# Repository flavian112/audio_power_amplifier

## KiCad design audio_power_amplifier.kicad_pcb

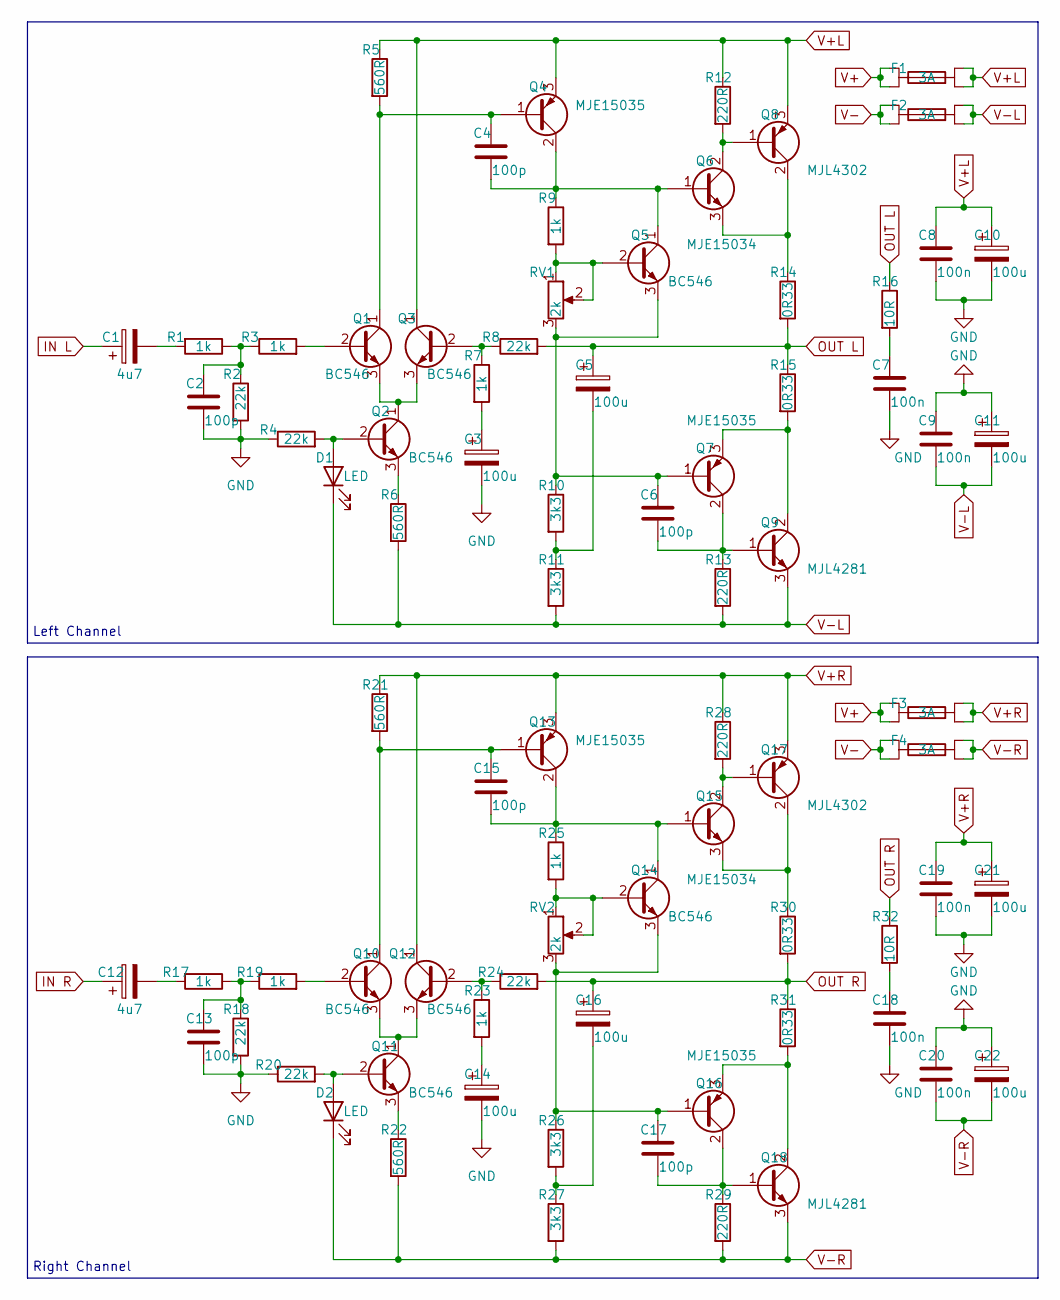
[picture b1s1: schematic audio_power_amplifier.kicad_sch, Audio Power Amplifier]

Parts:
C1, C12: 4u7; CP_Radial_D5.0mm_P2.00mm
C2, C4, C6, C13, C15, C17: 100p; C_Rect_L7.2mm_W4.5mm_P5.00mm_FKS2_FKP2_MKS2_MKP2
C3, C5, C10, C11, C14, C16, C21, C22: 100u; CP_Radial_D10.0mm_P5.00mm
C7, C8, C9, C18, C19, C20: 100n; C_Rect_L10.0mm_W2.5mm_P7.50mm_MKS4
D1, D2: LED; LED_D5.0mm
F1, F2, F3, F4: 3A; Fuseholder_Cylinder-5x20mm_Schurter_0752
Q1, Q2, Q3, Q5, Q10, Q11, Q12, Q14: BC546; TO-92_Wide
Q4, Q7, Q13, Q16: MJE15035; TO-220-3_Vertical
Q6, Q15: MJE15034; TO-220-3_Vertical
Q8, Q17: MJL4302; TO-264-3_Horizontal_TabUp
Q9, Q18: MJL4281; TO-264-3_Horizontal_TabUp
R1, R3, R7, R9, R17, R19, R23, R25: 1k; R_Axial_DIN0207_L6.3mm_D2.5mm_P7.62mm_Horizontal
R2, R4, R8, R18, R20, R24: 22k; R_Axial_DIN0207_L6.3mm_D2.5mm_P7.62mm_Horizontal
R5, R6, R21, R22: 560R; R_Axial_DIN0207_L6.3mm_D2.5mm_P7.62mm_Horizontal
R10, R11, R26, R27: 3k3; R_Axial_DIN0411_L9.9mm_D3.6mm_P12.70mm_Horizontal
R12, R13, R28, R29: 220R; R_Axial_DIN0207_L6.3mm_D2.5mm_P7.62mm_Horizontal
R14, R15, R30, R31: 0R33; R_Axial_Power_L25.0mm_W6.4mm_P27.94mm
R16, R32: 10R; R_Axial_DIN0411_L9.9mm_D3.6mm_P12.70mm_Horizontal
RV1, RV2: 2k; Potentiometer_Bourns_3339P_Vertical

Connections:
GND: C2.2, C3.2, C7.2, C8.2, C9.1, C10.2, C11.1, C13.2, C14.2, C18.2, C19.2, C20.1, C21.2, C22.1, R2.2, R4.1, R18.2, R20.1
IN L: C1.1
IN R: C12.1
unnamed: C1.2, R1.2
unnamed: C2.1, R1.1, R2.1, R3.1
unnamed: C3.1, R7.2
unnamed: C4.1, Q1.1 (C), Q4.1 (B), R5.2
unnamed: C4.2, Q4.2 (C), Q5.1 (C), Q6.1 (B), R9.1
unnamed: C5.2, R10.2, R11.1
unnamed: C6.1, Q5.3 (E), Q7.1 (B), R10.1, RV1.3
unnamed: C6.2, Q7.2 (C), Q9.1 (B), R13.1
unnamed: C7.1, R16.2
unnamed: C12.2, R17.2
unnamed: C13.1, R17.1, R18.1, R19.1
unnamed: C14.1, R23.2
unnamed: C15.1, Q10.1 (C), Q13.1 (B), R21.2
unnamed: C15.2, Q13.2 (C), Q14.1 (C), Q15.1 (B), R25.1
unnamed: C16.2, R26.2, R27.1
unnamed: C17.1, Q14.3 (E), Q16.1 (B), R26.1, RV2.3
unnamed: C17.2, Q16.2 (C), Q18.1 (B), R29.1
unnamed: C18.1, R32.2
unnamed: D1.2 (A), Q2.2 (B), R4.2
unnamed: D2.2 (A), Q11.2 (B), R20.2
unnamed: Q1.2 (B), R3.2
unnamed: Q1.3 (E), Q2.1 (C), Q3.3 (E)
unnamed: Q2.3 (E), R6.1
unnamed: Q3.2 (B), R7.1, R8.1
unnamed: Q5.2 (B), R9.2, RV1.1, RV1.2
unnamed: Q6.2 (C), Q8.1 (B), R12.2
unnamed: Q6.3 (E), Q8.2 (C), R14.1
unnamed: Q7.3 (E), Q9.2 (C), R15.2
unnamed: Q10.2 (B), R19.2
unnamed: Q10.3 (E), Q11.1 (C), Q12.3 (E)
unnamed: Q11.3 (E), R22.1
unnamed: Q12.2 (B), R23.1, R24.1
unnamed: Q14.2 (B), R25.2, RV2.1, RV2.2
unnamed: Q15.2 (C), Q17.1 (B), R28.2
unnamed: Q15.3 (E), Q17.2 (C), R30.1
unnamed: Q16.3 (E), Q18.2 (C), R31.2
OUT L: C5.1, R8.2, R14.2, R15.1, R16.1
OUT R: C16.1, R24.2, R30.2, R31.1, R32.1
V+: F1.1, F1.2, F3.1, F3.2
V+L: C8.1, C10.1, F1.3, F1.4, Q3.1 (C), Q4.3 (E), Q8.3 (E), R5.1, R12.1
V+R: C19.1, C21.1, F3.3, F3.4, Q12.1 (C), Q13.3 (E), Q17.3 (E), R21.1, R28.1
V-: F2.1, F2.2, F4.1, F4.2
V-L: C9.2, C11.2, D1.1 (K), F2.3, F2.4, Q9.3 (E), R6.2, R11.2, R13.2
V-R: C20.2, C22.2, D2.1 (K), F4.3, F4.4, Q18.3 (E), R22.2, R27.2, R29.2

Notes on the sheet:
Right Channel
Left Channel

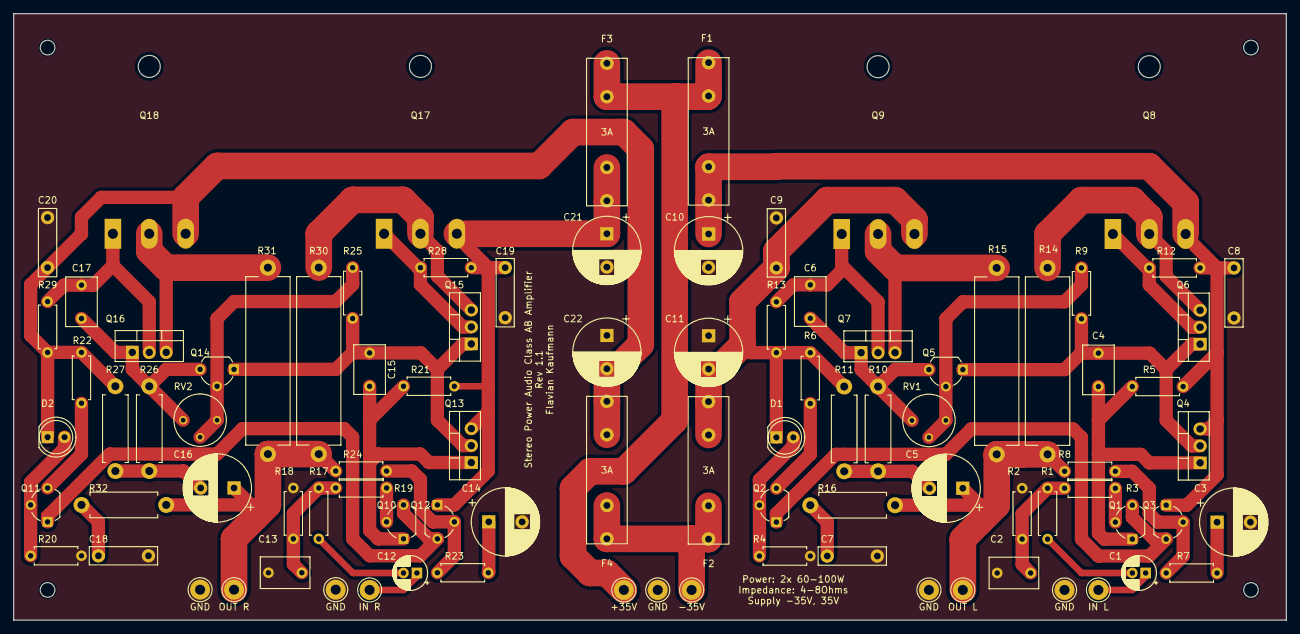
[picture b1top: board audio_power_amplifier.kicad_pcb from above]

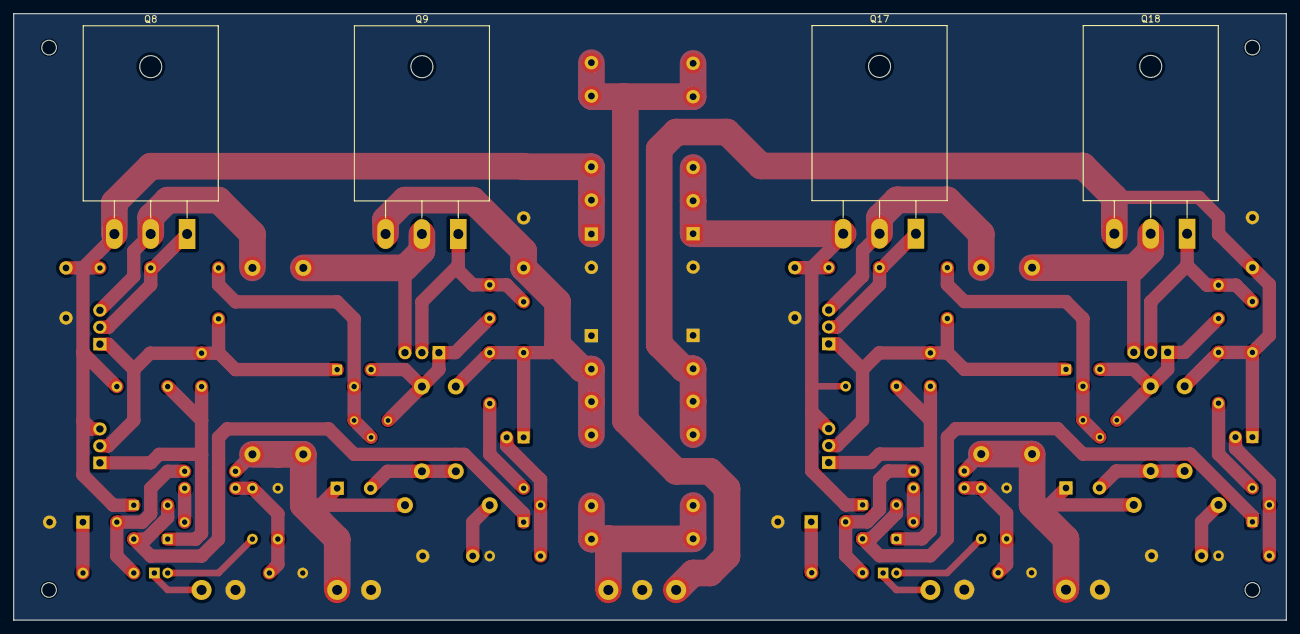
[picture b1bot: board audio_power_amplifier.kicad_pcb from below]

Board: 2 copper layers, 190.7 x 90.9 mm, 80 parts (4 on the bottom side), 45 nets.

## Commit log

2024-02-04 cosmetics
